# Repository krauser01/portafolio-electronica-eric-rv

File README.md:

# Portafolio de Electrónica y Sistemas Embebidos - Ing. Electrónico Eric Rodríguez Vásquez

¡Hola! Soy Eric, Ingeniero Electrónico.
Este repositorio centraliza mis proyectos de hardware, firmware, simulaciones y artículos técnicos.

## 📂 Estructura del Repositorio

- **`01_proyectos/`**: Diseño de hardware, firmware y documentación de proyectos completos.
  - `01_MVP_Calibrador_Señales_Industriales-(0-10V _4-20mA)`: Emulador de señales analógicas Industriales con ESP32
  - `02_fuente_lineal_lm317`: Fuente de poder analógica regulable (En progreso).
  - `03_proximo_proyecto`: [Título y estado del proyecto]
- **`02_articulos_tutoriales/`**: Guías técnicas, notas de aplicación y resolución de problemas.
- **`recursos/`**: Librerías de KiCad, footprints personalizados y scripts de utilidad.

## 🛠️ Stack Tecnológico

- **Hardware:** STM32, ESP32, AVR, PIC, ARM Cortex-M.
- **Software/Firmware:** C/C++, HAL/LL, ESP-IDF, FreeRTOS, PlatformIO, STM32CubeIDE.
- **EDA & Simulación:** KiCad, LTspice.
- **Herramientas:** Osciloscopio, analizador lógico, SWD/JTAG, GDB.

## 📬 Contacto
- LinkedIn: 
- Email: ing.ericrodriguezv@gmail.com

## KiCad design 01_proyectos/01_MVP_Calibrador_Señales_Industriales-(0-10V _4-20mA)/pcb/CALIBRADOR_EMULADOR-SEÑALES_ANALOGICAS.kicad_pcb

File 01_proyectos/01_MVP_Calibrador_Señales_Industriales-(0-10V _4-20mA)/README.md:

# 🎛️ Calibrador y Emulador Portátil de Señales Industriales (ESP32)

## 📌 Resumen Ejecutivo
Diseño y desarrollo de un instrumento de diagnóstico portátil (MVP) para la validación física de lazos de control en el **Complejo Termoeléctrico Planta Centro (CORPOELEC)**. El sistema emula y mide señales analógicas industriales (**4-20 mA** y **0-10 V**), permitiendo a las cuadrillas de instrumentación verificar la integridad del cableado y la respuesta de tarjetas de E/S sin depender de equipos de calibración importados de alto costo o forzamientos por software.

## 📸 Galería del Proyecto
| Prototipo Final | PCB y Ensamble | Pruebas en Campo |
| :---: | :---: | :---: |
|  |  |  |
| *Vista frontal con TFT ST7735* | *Layout y soldadura* | *Validación en banco de pruebas* |

> 💡 *Puedes ver el proceso completo de construcción y pruebas en la carpeta [`/pics`](pics/).*

## 🚀 Impacto y Métricas Clave
- 💰 **Reducción de Costos del 96%**: Costo de materiales de **$65.50 USD** frente a los $1,650 USD de un Fluke 715.
- 🎯 **Precisión Industrial**: Error máximo reducido al **0.25% del Span** (Corriente) y **0.60% del FS** (Voltaje) tras calibración algorítmica.
- 📈 **Estabilidad de Señal**: >98% en pruebas continuas, gracias a filtrado analógico (RC 15.9Hz) y digital (Oversampling + Promedio Móvil).

## 🏗️ Arquitectura del Sistema

### Hardware
| Componente | Especificación / Función |
| :--- | :--- |
| **MCU** | ESP32 (Doble núcleo, 240MHz, ADC 12-bit, PWM/LEDC) |
| **Acondicionamiento Analógico** | LM358 (Buffers/Amplificadores), Shunt 150Ω 1% (Metal Film) |
| **Fuentes de Poder** | Li-Ion 3.7V + TP4056, Boost MT3608 (5V), Boost XL6009 (24V para lazo activo) |
| **Interfaz** | TFT 1.8" ST7735 (SPI), Botones táctiles, LEDs de estado |
| **Protección** | Diodos Zener 3.3V en entradas ADC, Filtros RC pasabajos (fc ≈ 15.9 Hz) |

### Firmware y Procesamiento de Señal
- **Lenguaje**: C++ (Entorno PlatformIO / Arduino Framework).
- **Arquitectura**: Máquina de estados finita (FSM) para la interfaz de usuario, tareas no bloqueantes.
- **Metrología por Software**: Algoritmo de calibración de 2 puntos ($Y = mX + b$) con almacenamiento de coeficientes en **NVS** (Non-Volatile Storage).
- **Filtrado Digital**: Oversampling del ADC interno y filtro de promedio móvil para mitigar ruido EMI industrial (conmutación de tiristores, motores).

## 📂 Estructura del Repositorio
```text
├── Docs/           # Manual de usuario, reporte de calibración, BOM y memorias de cálculo
├── Firmware/       # Código fuente C++ (PlatformIO) con drivers y lógica de calibración
├── Pcb/            # Layout KiCad, Gerbers y renders 3D
├── Schematics/     # Esquemáticos KiCad y PDFs exportados
├── pics/           # Galería fotográfica del paso a paso (Protoboard, PCB, Campo)
└── README.md       # Este archivo

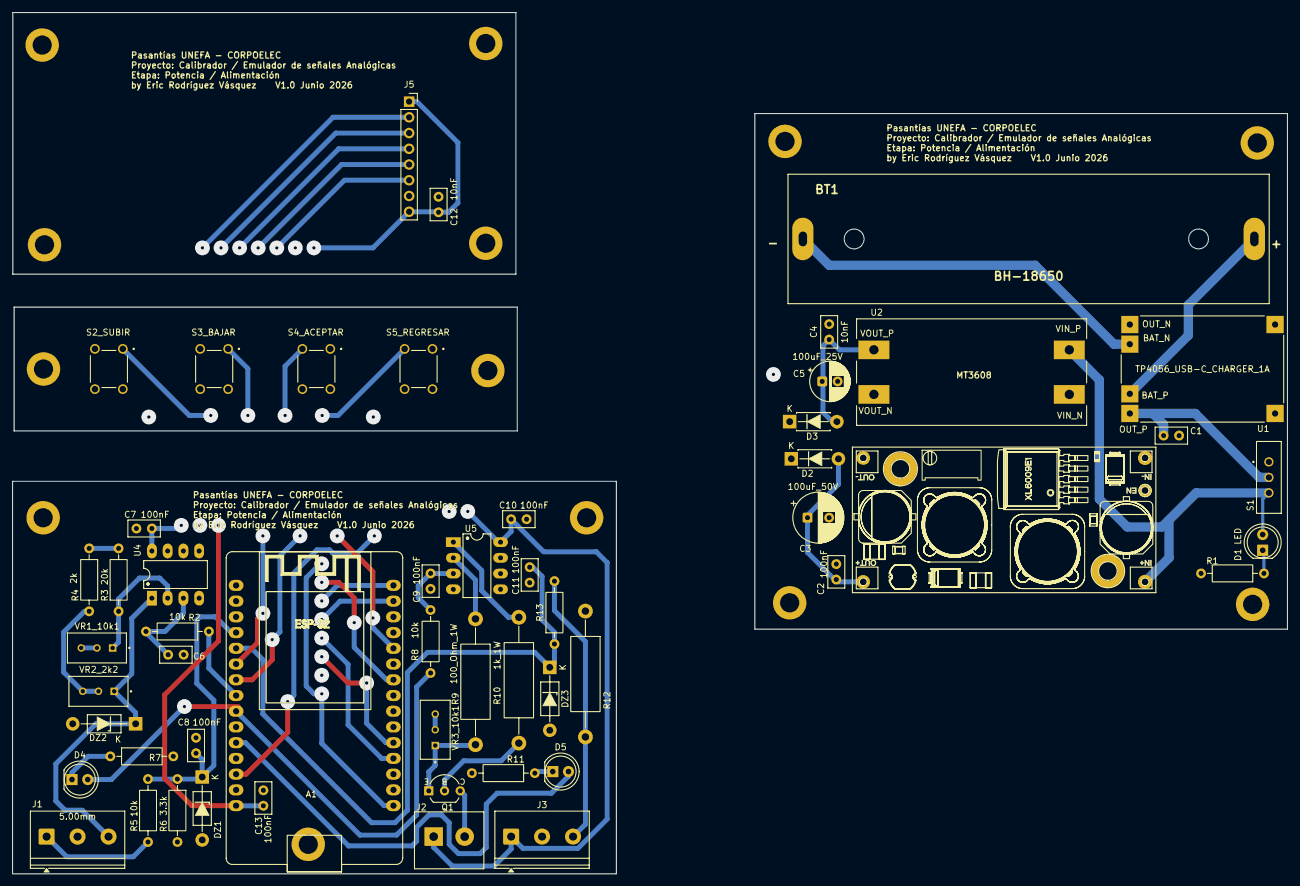
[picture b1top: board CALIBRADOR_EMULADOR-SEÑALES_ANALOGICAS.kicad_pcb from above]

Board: 2 copper layers, 205.9 x 139.1 mm, 54 parts (0 on the bottom side), 41 nets.

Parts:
A1: ESP32_DevKit_V1_DOIT_30GPIOs; DOIT_ESP32_DEVKIT_30Pins
BT1: BH-18650; BAT_BH-18650-PC
C1, C4, C12: 10nF; C_Disc_D5.0mm_W2.5mm_P2.50mm
C2, C6, C7, C8, C9, C10, C11, C13: 100nF; C_Disc_D5.0mm_W2.5mm_P2.50mm
C3: 100uF_50V; CP_Radial_D8.0mm_P3.50mm
C5: 100uF_25V; CP_Radial_D6.3mm_P2.50mm
D1, D4, D5: LED; LED_D5.0mm
D2, D3: 1N4007; D_DO-41_SOD81_P7.62mm_Horizontal
DZ1, DZ3: 1N4728A; D_DO-41_SOD81_P10.16mm_Horizontal_Zener
DZ2: 1N4740A; D_DO-41_SOD81_P10.16mm_Horizontal_Zener
J1, J3: 5.00mm; TerminalBlock_Phoenix_PT-1,5-3-5.0-H_1x03_P5.00mm_Horizontal
J2: 5.00mm; TerminalBlock_OnShore_1x02_P5.00mm_Horizontal
J5: PINHD_1x8_Female; PinSocket_1x08_P2.54mm_Vertical
Q1: 2N2222A-TO92; TO-92_Inline_Wide_EBC
R1, R7, R11: Resistor; R_Axial_DIN0207_L6.3mm_D2.5mm_P10.16mm_Horizontal
R2, R5, R8: 10k; R_Axial_DIN0207_L6.3mm_D2.5mm_P10.16mm_Horizontal
R3: 20k; R_Axial_DIN0207_L6.3mm_D2.5mm_P10.16mm_Horizontal
R4: 2k; R_Axial_DIN0207_L6.3mm_D2.5mm_P10.16mm_Horizontal
R6: 3.3k; R_Axial_DIN0207_L6.3mm_D2.5mm_P10.16mm_Horizontal
R9: 100_Ohm_1W; R_Axial_DIN0414_L11.9mm_D4.5mm_P20.32mm_Horizontal
R10: 1k_1W; R_Axial_DIN0414_L11.9mm_D4.5mm_P20.32mm_Horizontal
R12: 150_ohm_1W; R_Axial_DIN0414_L11.9mm_D4.5mm_P20.32mm_Horizontal
R13: 1k; R_Axial_DIN0207_L6.3mm_D2.5mm_P10.16mm_Horizontal
S1: EG1218; SW_EG1218
S2_SUBIR, S3_BAJAR, S4_ACEPTAR, S5_REGRESAR: FSM8JH; SW_Push_button_6mm_FSM8JH
U1: TP4056_USB-C_CHARGER_1A; MODULE_TP4056_MICRO-USB_CHARGER_-_1A
U2: MT3608; MODULE_MT3608_DC-DC_STEP_UP_CONVERTER_2A_BOOSTER_MODULE
U3: XL6009; XL6009_Module
U4, U5: LM358N; DIP-8_W7.62mm_LongPads
VR1_10k1, VR2_2k2, VR3_10k1: 3296W-FM1-502; TRIMMER_3296W-FM1-502

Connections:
+5v_ESP32: A1.30 (VIN), C13.1, D3.1 (K)
+24V_OPAMP: C7.2, C10.2, D2.1 (K), J2.1, J3.1, U4.8 (V+), U5.8 (V+)
ADC_CURR_GPIO35: A1.20 (ADC1_CH7/D35), C11.2, DZ3.1 (K), R13.1
ADC_VOLT_GPIO34: A1.19 (ADC1_CH6/D34), C8.2, DZ1.1 (K), R5.2, R6.1
BTN_BACK_GPIO13: A1.28 (ADC2_CH4/D13), S5_REGRESAR.3
BTN_DOWN _GPIO33: A1.22 (ADC1_CH4/D32), S3_BAJAR.1, S3_BAJAR.3
BTN_OK_GPIO21: A1.11 (D21/SDA), S4_ACEPTAR.3
BTN_UP_GPIO32: A1.21 (ADC1_CH4/D32), S2_SUBIR.1, S2_SUBIR.3
CS_GPIO5: A1.5 (D4/ADC2_CH0), J5.6
DAC_CURR_GPIO26: A1.24 (DAC2/ADC2_CH9/D26), R8.1
DAC_VOLT_GPIO25: A1.23 (DAC1/ADC2_CH8/D25), R2.1
DC_AD_GPIO22: A1.14 (D22/SCL), J5.4
GND: A1.2 (GND), A1.29 (GND), C1.1, C2.2, C3.2, C4.2, C5.2, C6.2, C7.1, C8.1, C9.2, C10.1, C11.1, C12.1, C13.2, DZ1.2 (A), DZ2.2 (A), DZ3.2 (A), J1.2, J3.2, J5.7, R1.2, R6.2, R7.2, R11.2, R12.1, S2_SUBIR.2, S3_BAJAR.2, S4_ACEPTAR.2, S5_REGRESAR.2, U1.IN_N (IN-), U1.OUT_N (OUT-), U3.2 (IN-), U3.5 (OUT-), U4.4 (V-), U5.4 (V-), VR1_10k1.2, VR1_10k1.3, VR3_10k1.2, VR3_10k1.3
LED_CURR_GPIO14: A1.26 (ADC2_CH6/D14), D5.2
LED_VOLT_GPIO27: A1.25 (ADC2_CH7/D27), D4.2
unnamed: D1.1, R1.1
unnamed: C2.1, C3.1, D2.2 (A), U3.4 (OUT+)
unnamed: C4.1, C5.1, D3.2 (A)
unnamed: D4.1, R7.1
unnamed: D5.1, R11.1
unnamed: DZ2.1 (K), J1.3, U4.1, VR2_2k2.1
unnamed: J1.1, R5.1
unnamed: J2.2, Q1.3 (C)
unnamed: J3.3, R12.2, R13.2
unnamed: Q1.2 (B), R10.2
unnamed: Q1.1 (E), R9.2, VR3_10k1.1
unnamed: R3.2, R4.1
unnamed: R4.2, VR2_2k2.2, VR2_2k2.3
unnamed: R10.1, U5.1
unnamed: BT1.P, U1.BAT_P (BAT+)
unnamed: BT1.N, U1.BAT_N (BAT-)
unnamed: C1.2, S1.2, U1.OUT_P (OUT+)
unnamed: D1.2, S1.3, U3.1 (IN+)
unnamed: C6.1, R2.2, U4.3 (+)
unnamed: R3.1, U4.2 (-), VR1_10k1.1
unnamed: C9.1, R8.2, U5.3 (+)
unnamed: R9.1, U5.2 (-)
RESET_GPIO4: A1.4 (D2/ADC2_CH2), J5.5
SCK_GPIO18: A1.9 (D18), J5.2
SDA_MOSI__GPIO23: A1.15 (D23), J5.3
VCC_3V3: A1.1 (3.3V), C12.2, J5.1, J5.8

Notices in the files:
01_proyectos/01_MVP_Calibrador_Señales_Industriales-(0-10V _4-20mA)/README.md:
License: MIT
